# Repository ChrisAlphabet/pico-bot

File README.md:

# pico-bot
A two-wheeled self-balancing robot built around the Raspberry Pi Pico

## Useful resources
* https://datasheets.raspberrypi.com/pico/getting-started-with-pico.pdf
* https://datasheets.raspberrypi.com/picow/pico-w-datasheet.pdf
* https://datasheets.raspberrypi.com/rp2040/rp2040-datasheet.pdf 

Start code from a developer prompt so all the env variables are setup properly

## Notes
Mounting holes:
y: 30.6mm
x: 94.6mm 

cargo build --target thumbv7m-none-eabi

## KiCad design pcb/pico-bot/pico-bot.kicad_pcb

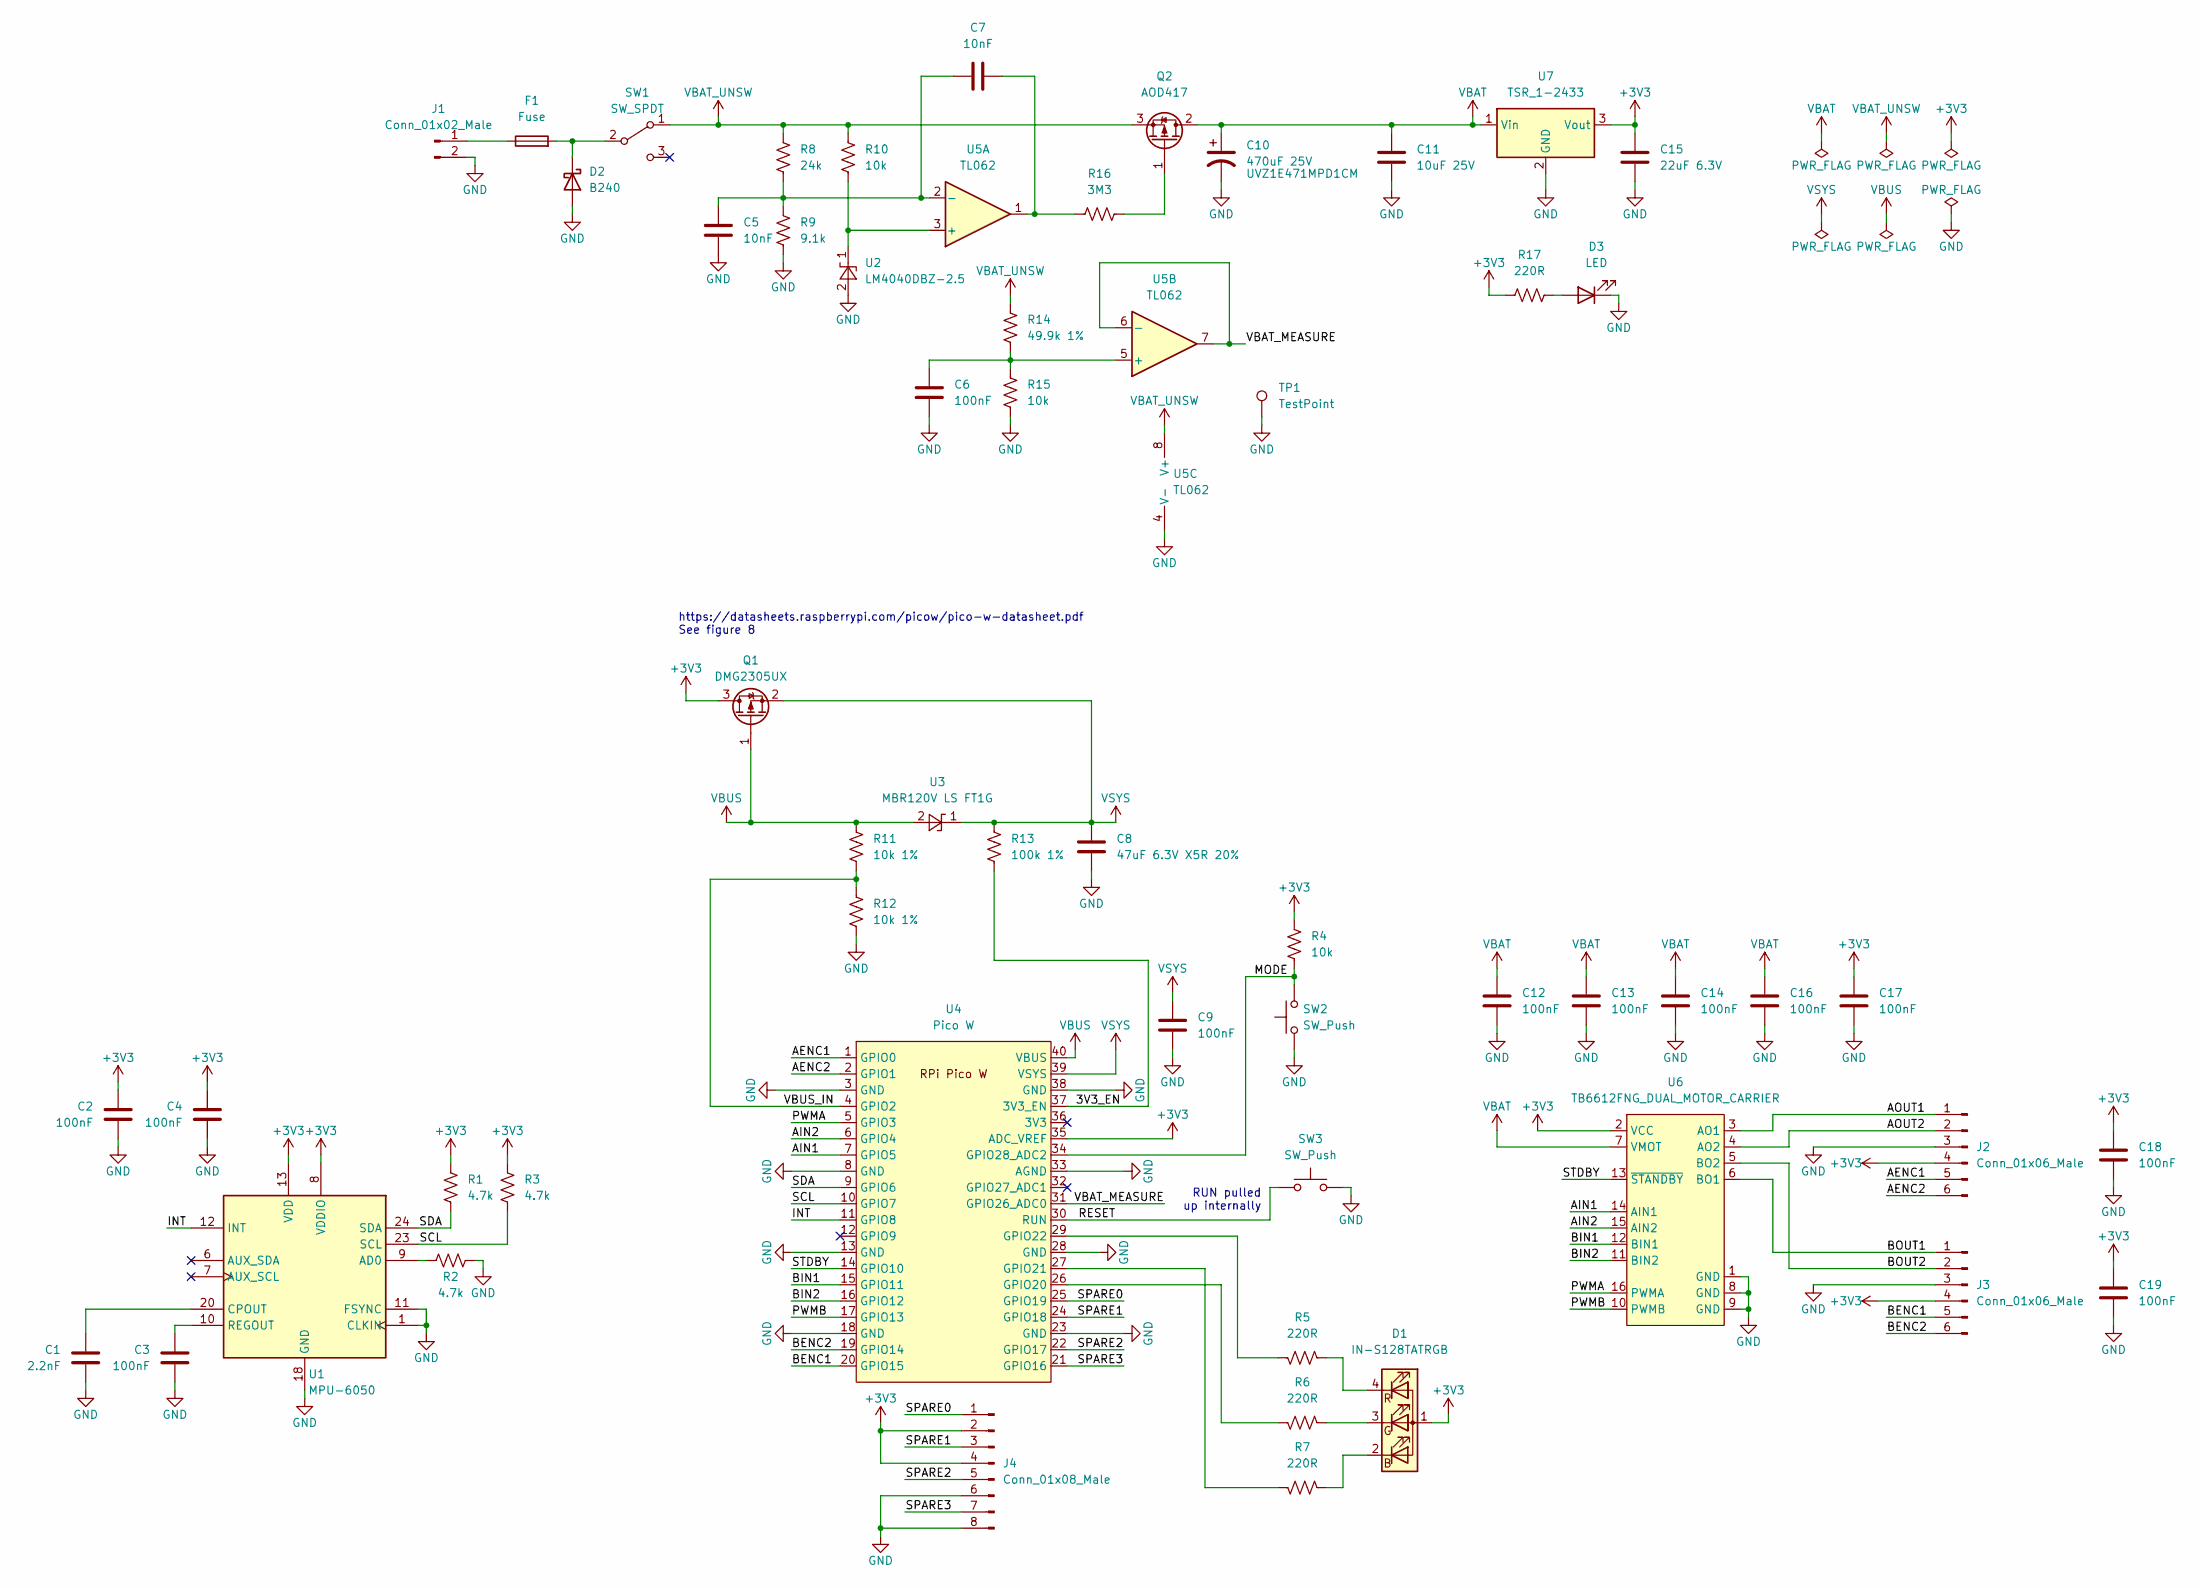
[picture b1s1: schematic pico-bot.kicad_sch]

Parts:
C1: 2.2nF; C_0805_2012Metric_Pad1.18x1.45mm_HandSolder
C2, C3, C4, C6, C9, C12, C13, C14, C16, C17, C18, C19: 100nF; C_0805_2012Metric_Pad1.18x1.45mm_HandSolder
C5, C7: 10nF; C_0805_2012Metric_Pad1.18x1.45mm_HandSolder
C8: 47uF 6.3V X5R 20%; C_0805_2012Metric_Pad1.18x1.45mm_HandSolder
C10: 470uF 25V; CP_Radial_D10.0mm_P5.00mm; PartNumber UVZ1E471MPD1CM
C11: 10uF 25V; C_1206_3216Metric_Pad1.33x1.80mm_HandSolder
C15: 22uF 6.3V; C_0805_2012Metric_Pad1.18x1.45mm_HandSolder
D1: IN-S128TATRGB; LED_RGB_1210
D2: B240; D_SMB
D3: LED; LED_0805_2012Metric_Pad1.15x1.40mm_HandSolder
F1: Fuse; Fuseholder_Littelfuse_Nano2_154x
J1: Conn_01x02_Male; PinSocket_1x02_P2.54mm_Vertical
J2, J3: Conn_01x06_Male; PinHeader_1x06_P2.54mm_Vertical
J4: Conn_01x08_Male; PinHeader_2x04_P2.54mm_Vertical
Q1: DMG2305UX; SOT-23
Q2: AOD417; TO-252-2
R1, R2, R3: 4.7k; R_0805_2012Metric_Pad1.20x1.40mm_HandSolder
R4, R10, R15: 10k; R_0805_2012Metric_Pad1.20x1.40mm_HandSolder
R5, R6, R7, R17: 220R; R_0805_2012Metric_Pad1.20x1.40mm_HandSolder
R8: 24k; R_0805_2012Metric_Pad1.20x1.40mm_HandSolder
R9: 9.1k; R_0805_2012Metric_Pad1.20x1.40mm_HandSolder
R11, R12: 10k 1%; R_0805_2012Metric_Pad1.20x1.40mm_HandSolder
R13: 100k 1%; R_0805_2012Metric_Pad1.20x1.40mm_HandSolder
R14: 49.9k 1%; R_0805_2012Metric_Pad1.20x1.40mm_HandSolder
R16: 3M3; R_0805_2012Metric_Pad1.20x1.40mm_HandSolder
SW1: SW_SPDT; 1101M2S3CRE2
SW2, SW3: SW_Push; SW_PUSH_6mm
TP1: TestPoint; PinHeader_1x01_P2.54mm_Vertical
U1: MPU-6050; InvenSense_QFN-24_4x4mm_P0.5mm
U2: LM4040DBZ-2.5; SOT-23
U3: MBR120V LS FT1G; D_SOD-123F
U4: Pico W; RPi_Pico_SMD_TH
U5: TL062; SOIC-8-1EP_3.9x4.9mm_P1.27mm_EP2.29x3mm
U6: TB6612FNG_DUAL_MOTOR_CARRIER; TB6612FNG-CARRIER
U7: TSR_1-2433; Converter_DCDC_TRACO_TSR-1_THT

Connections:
+3V3: C2.2, C4.2, C15.2, C17.2, C18.2, C19.2, D1.1 (A), J2.4, J3.4, J4.2, J4.4, Q1.3 (D), R1.2, R3.2, R4.2, R17.1, U1.8 (VDDIO), U1.13 (VDD), U4.35 (ADC_VREF), U6.2 (VCC), U7.3 (Vout)
/3V3_EN: R13.1, U4.37 (3V3_EN)
/AENC1: J2.5, U4.1 (GPIO0)
/AENC2: J2.6, U4.2 (GPIO1)
/AIN1: U4.7 (GPIO5), U6.14 (AIN1)
/AIN2: U4.6 (GPIO4), U6.15 (AIN2)
/AOUT1: J2.1, U6.3 (AO1)
/AOUT2: J2.2, U6.4 (AO2)
/BENC1: J3.5, U4.20 (GPIO15)
/BENC2: J3.6, U4.19 (GPIO14)
/BIN1: U4.15 (GPIO11), U6.12 (BIN1)
/BIN2: U4.16 (GPIO12), U6.11 (BIN2)
/BOUT1: J3.1, U6.6 (BO1)
/BOUT2: J3.2, U6.5 (BO2)
/INT: U1.12 (INT), U4.11 (GPIO8)
/MODE: R4.1, SW2.2, U4.34 (GPIO28_ADC2)
/PWMA: U4.5 (GPIO3), U6.16 (PWMA)
/PWMB: U4.17 (GPIO13), U6.10 (PWMB)
/RESET: SW3.1, U4.30 (RUN)
/SCL: R3.1, U1.23 (SCL), U4.10 (GPIO7)
/SDA: R1.1, U1.24 (SDA), U4.9 (GPIO6)
/SPARE0: J4.1, U4.25 (GPIO19)
/SPARE1: J4.3, U4.24 (GPIO18)
/SPARE2: J4.5, U4.22 (GPIO17)
/SPARE3: J4.7, U4.21 (GPIO16)
/STDBY: U4.14 (GPIO10), U6.13 (~STANDBY)
/VBAT_MEASURE: U4.31 (GPIO26_ADC0), U5.6 (-), U5.7
/VBUS_IN: R11.1, R12.2, U4.4 (GPIO2)
GND: C1.1, C2.1, C3.1, C4.1, C5.1, C6.1, C8.1, C9.1, C10.2, C11.1, C12.1, C13.1, C14.1, C15.1, C16.1, C17.1, C18.1, C19.1, D2.2 (A), D3.1 (K), J1.2, J2.3, J3.3, J4.6, J4.8, R2.1, R9.1, R12.1, R15.1, SW2.1, SW3.2, TP1.1, U1.1 (CLKIN), U1.11 (FSYNC), U1.18 (GND), U2.2 (A), U4.3 (GND), U4.8 (GND), U4.13 (GND), U4.18 (GND), U4.23 (GND), U4.28 (GND), U4.33 (AGND), U4.38 (GND), U5.4 (V-), U6.1 (GND), U6.8 (GND), U6.9 (GND), U7.2 (GND)
unnamed: C1.2, U1.20 (CPOUT)
unnamed: C3.2, U1.10 (REGOUT)
unnamed: C5.2, C7.1, R8.1, R9.2, U5.2 (-)
unnamed: C6.2, R14.1, R15.2, U5.5 (+)
unnamed: C7.2, R16.1, U5.1
unnamed: D1.2 (BK), R7.1
unnamed: D1.3 (GK), R6.1
unnamed: D1.4 (RK), R5.1
unnamed: D2.1 (K), F1.2, SW1.2 (B)
unnamed: D3.2 (A), R17.2
unnamed: F1.1, J1.1
unnamed: Q2.1 (G), R16.2
unnamed: R2.2, U1.9 (AD0)
unnamed: R5.2, U4.29 (GPIO22)
unnamed: R6.2, U4.26 (GPIO20)
unnamed: R7.2, U4.27 (GPIO21)
unnamed: R10.1, U2.1 (K), U5.3 (+)
VBAT: C10.1, C11.2, C12.2, C13.2, C14.2, C16.2, Q2.2 (D), U6.7 (VMOT), U7.1 (Vin)
VBAT_UNSW: Q2.3 (S), R8.2, R10.2, R14.2, SW1.1 (A), U5.8 (V+)
VBUS: Q1.1 (G), R11.2, U3.2 (A), U4.40 (VBUS)
VSYS: C8.2, C9.2, Q1.2 (S), R13.2, U3.1 (K), U4.39 (VSYS)

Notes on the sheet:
RUN pulled up internally
https://datasheets.raspberrypi.com/picow/pico-w-datasheet.pdf See figure 8

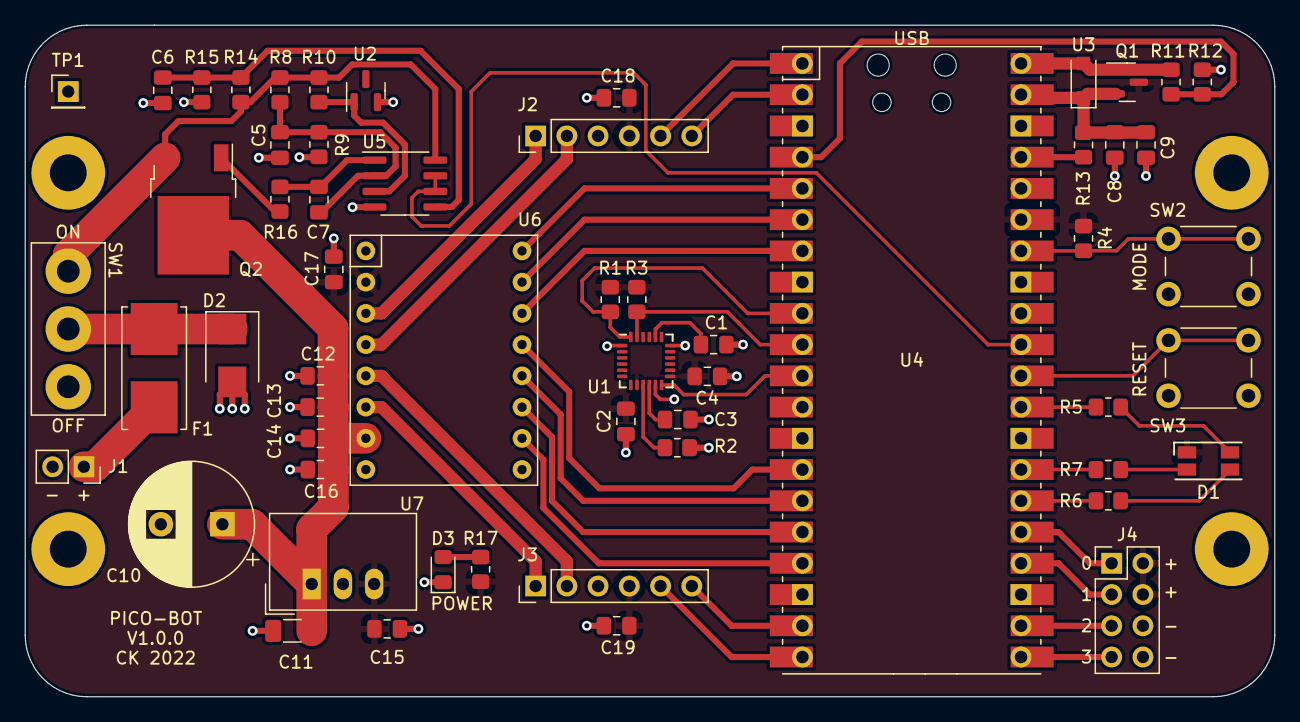
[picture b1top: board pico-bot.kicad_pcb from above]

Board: 2 copper layers, 101.6 x 54.6 mm, 57 parts (0 on the bottom side), 50 nets.

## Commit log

2022-10-13 Create kicad project, add motor driver, ignore kicad backups
2022-10-15 Add tb6612fng and mpu6050
2022-10-15 Add power circuit up to regulator
2022-10-15 Finish power circuit
2022-10-15 Add motor controller and imu circuits, create rpi pico w
2022-10-15 Progress commit
2022-10-16 Add pico external power circuit, wire up pico
2022-10-16 Add sw, rgb, update footprints
2022-10-16 Use mpu6050 directly instead of carrier board
2022-10-16 Add annotations to schematic
2022-10-16 Add pico-sdk as a submodule, add useful links to readme
2022-10-16 Prove setup works by running integrating the helloworld example
2022-10-16 Add a wip schematic pdf
2022-10-17 Add ERC fixes, route unused GPIO and pwr/gnd to pins
2022-10-17 Update schematic pdf
2022-10-20 Fix missing footprints, add parts to PCB
2022-10-22 Define mounting hole locations
2022-10-22 Fix readme
2022-10-25 Group circuits together on PCB
2022-10-25 Group undervoltage protection circuit components
2022-10-29 Add rough board outline
2022-10-29 Finish init placement of components
2022-10-29 Route power and input protection
2022-10-30 Partial route mpu6050
2022-10-30 Rework pin allocation to ease layout
2022-10-31 Center and route MPU-6050
2022-10-31 Route pico power select circuit
2022-10-31 Route all except power and ground
2022-11-01 Add pours, pour currently broken
2022-11-02 Update pour clearance and repour, now all nets are connected
2022-11-02 Address DRC warnings
2022-11-02 Update silkscreen
2022-11-06 Remove c sdk
2022-11-06 Remove sdk folder
2022-11-06 Remove sdk cmake
2022-11-06 Remove playground folder
2022-11-06 Add simple rust example
2022-11-06 Remove rust project (not so simple after all)
2022-11-06 Add pico project template
2022-11-06 Update to use example from rp-rs
2022-11-10 Add pwm from rp-hal example
